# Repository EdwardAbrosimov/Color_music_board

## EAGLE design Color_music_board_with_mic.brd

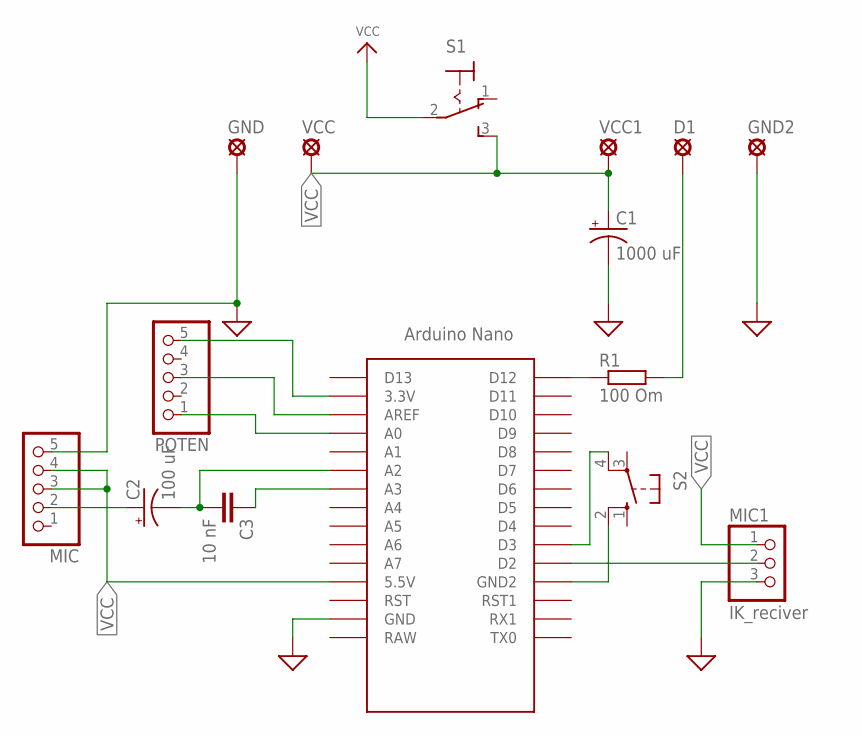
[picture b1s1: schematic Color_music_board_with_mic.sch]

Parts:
C1: 1000 uF; TT5D10
C2: 100 uF; E2,5-6
C3: 10 nF; C2.5-2
D1: SE14
GND, GND2: SE14
MIC: PINHD-1X5; 1X05
MIC1: IK_reciver; 1X03
POTEN: PINHD-1X5; 1X05
R1: 100 Om; 0207/7
S1: 320-916
S2: 10-XX; B3F-10XX
U$1: NANO
VCC, VCC1: SE14

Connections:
GND: C1.-, GND.MP, GND2.MP, MIC.5, MIC1.3, U$1.GND
unnamed: D1.MP, R1.2
unnamed: R1.1, U$1.D12
unnamed: C2.+, MIC.2
unnamed: MIC1.2, U$1.D2
unnamed: C2.-, C3.2, U$1.A2
unnamed: C3.1, U$1.A3
unnamed: POTEN.5, U$1.3.3V
unnamed: POTEN.3, U$1.AREF
unnamed: POTEN.1, U$1.A0
unnamed: S2.2 (S1), U$1.GND1 (GND2)
unnamed: S2.4 (P1), U$1.D3
VCC: C1.+, MIC.3, MIC.4, MIC1.1, S1.2, S1.3 (S), U$1.5V (5.5V), VCC.MP, VCC1.MP

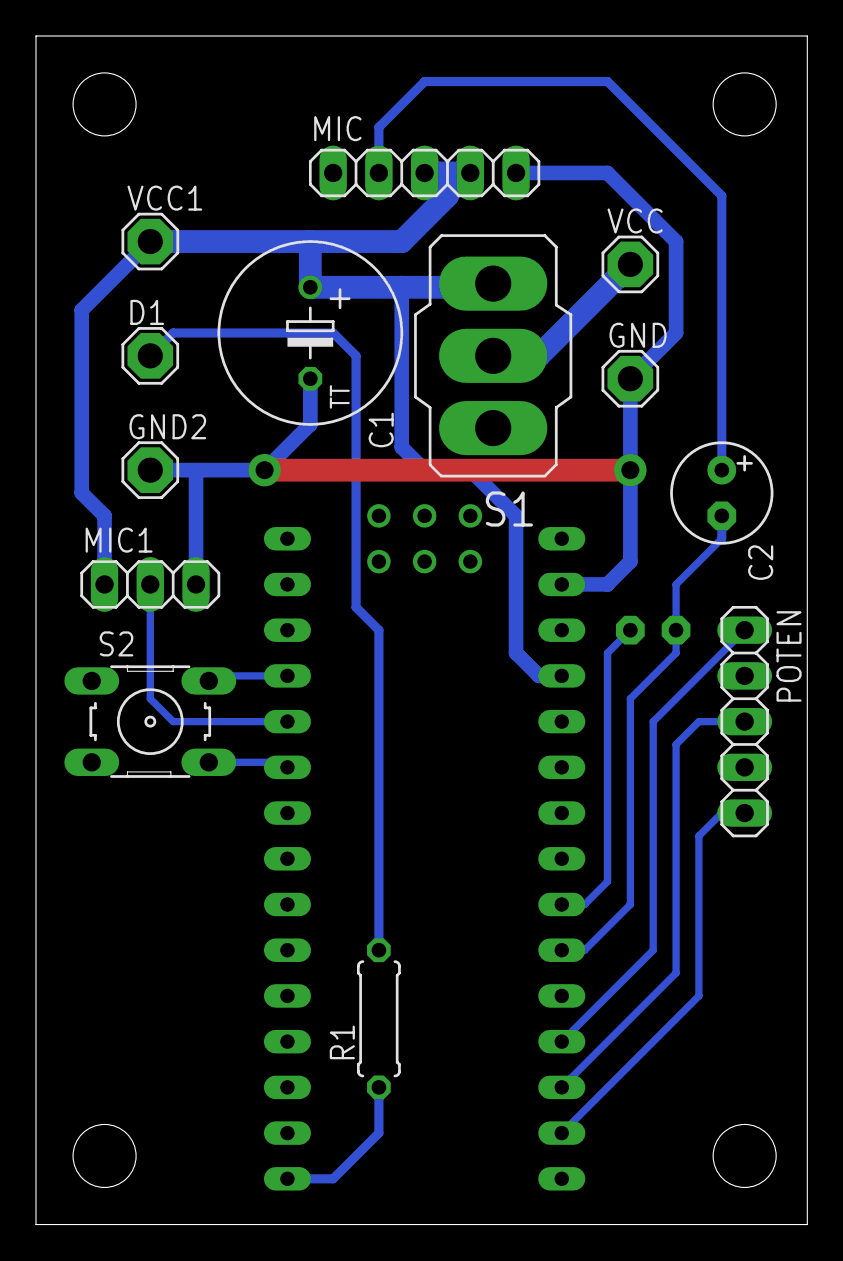
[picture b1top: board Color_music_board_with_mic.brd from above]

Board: 2 copper layers, 42.9 x 66.0 mm, 15 parts (1 on the bottom side), 13 nets.

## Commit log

2018-06-15 Adding project scheme
2018-06-17 Added board
2018-06-17 Fixed switch on the power line. Added a template for printing
